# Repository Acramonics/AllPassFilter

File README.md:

All Pass Filter
===============

Circuit by Jake Rothman, Practical Electronics, June 2026

KiCad and PCB by Andrew Martin, acramonics, May 2026

Background
----------

This is a universal all-pass filter with 8 cascaded all-pass sections
allowing a frequency-dependent phase shift.

See the April, May and June 2026 issues of Practical Electronics for details.

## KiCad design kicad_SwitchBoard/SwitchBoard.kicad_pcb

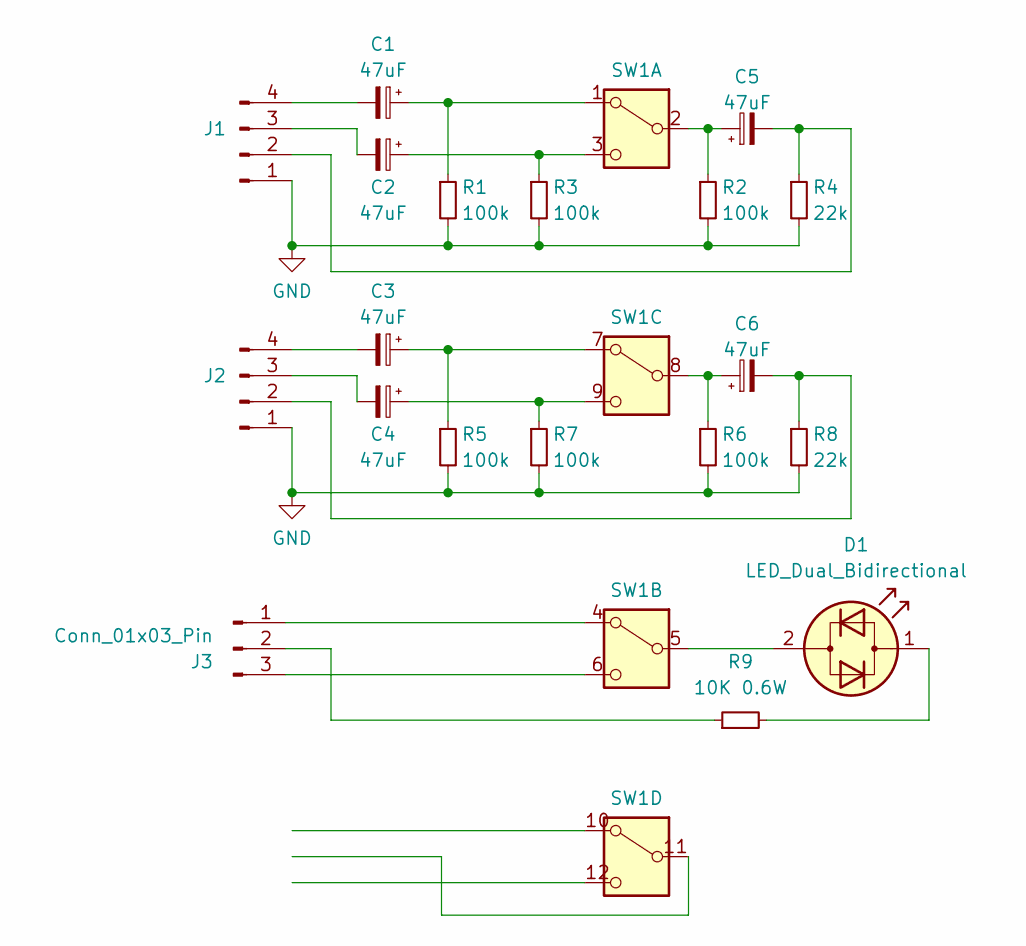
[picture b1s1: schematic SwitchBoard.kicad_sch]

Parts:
C1, C2, C3, C4, C5, C6: 47uF; CP_Radial_D5.0mm_P2.50mm
D1: LED_Dual_Bidirectional; LED_D5.0mm
J1, J2: Conn_01x04_Pin; Molex_KK-254_AE-6410-04A_1x04_P2.54mm_Vertical
J3: Conn_01x03_Pin; Molex_KK-254_AE-6410-03A_1x03_P2.54mm_Vertical
R1, R2, R3, R5, R6, R7: 100k; R_Axial_DIN0207_L6.3mm_D2.5mm_P10.16mm_Horizontal
R4, R8: 22k; R_Axial_DIN0207_L6.3mm_D2.5mm_P10.16mm_Horizontal
R9: 10K 0.6W; R_Axial_DIN0411_L9.9mm_D3.6mm_P12.70mm_Horizontal
SW1: SW_4PDT_x4; PushSwitch_4PDT_2x6Pin_P3.18x2.8

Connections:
GND: J1.1, J2.1, R1.2, R2.2, R3.2, R4.2, R5.2, R6.2, R7.2, R8.2
unnamed: D1.2 (AK), SW1.5 (B)
unnamed: D1.1 (KA), R9.2
unnamed: C5.2, J1.2, R4.1
unnamed: C2.2, J1.3
unnamed: C1.2, J1.4
unnamed: C6.2, J2.2, R8.1
unnamed: C4.2, J2.3
unnamed: C3.2, J2.4
unnamed: J3.1, SW1.4 (A)
unnamed: J3.2, R9.1
unnamed: J3.3, SW1.6 (C)
unnamed: C1.1, R1.1, SW1.1 (A)
unnamed: C5.1, R2.1, SW1.2 (B)
unnamed: C2.1, R3.1, SW1.3 (C)
unnamed: C3.1, R5.1, SW1.7 (A)
unnamed: C6.1, R6.1, SW1.8 (B)
unnamed: C4.1, R7.1, SW1.9 (C)

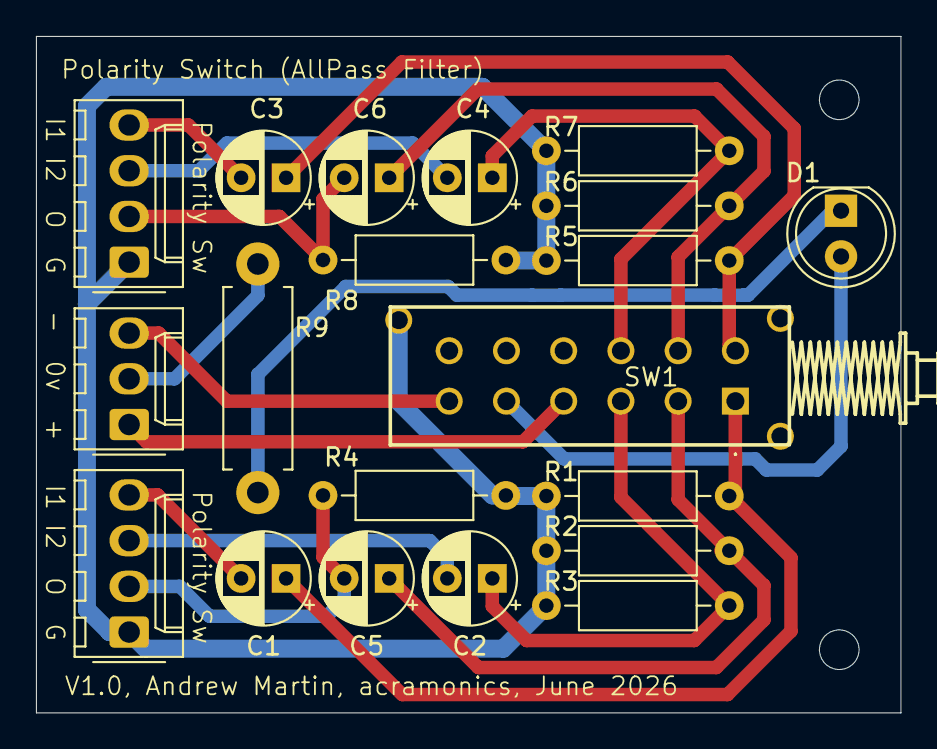
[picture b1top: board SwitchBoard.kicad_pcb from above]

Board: 2 copper layers, 48.0 x 37.6 mm, 20 parts (0 on the bottom side), 18 nets.

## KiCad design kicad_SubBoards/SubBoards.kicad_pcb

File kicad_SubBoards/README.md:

This uses the *SamacSys* footprint for the Alpha switch available via
the Mouser web site and directly from
[Component Search Engine](https://componentsearchengine.com/search?term=SR2612F-0112-21R0B-D8-N)

Using the Library
-----------------

First create a path name for the SamacSys Library:

1. In the main KiCad window, select `Preferences>Configure Paths`

2. Click the `+` sign and add a path called `KICAD_SAMACSYS_LIBS` and pointing to wherever the directory is containing the `SamacSys_Parts.lib` file.

3. Click OK

Next, configure the symbol library:

1. In the main KiCad window, select `Preferences>Manage Symbol Libraries`
2. Click the `+` sign and add a new library:

- `Nickname` = `SamacSys`
- `Library Path` = `${KICAD_SAMACSYS_LIBS}/SamacSys_Parts.kicad_sym`
- `Description` = `SamacSys Symbols`

and click `OK`.

Finally, configure the footprints library:

1. In the main KiCad window, select `Preferences>Manage Footprint Libraries`
2. Click the `+` sign and add a new library:

- `Nickname` = `SamacSys`
- `Library Path` = `${KICAD_SAMACSYS_LIBS}/SamacSys_Parts.pretty`
- `Description` = `SamacSys Footprints`

and click `OK`.

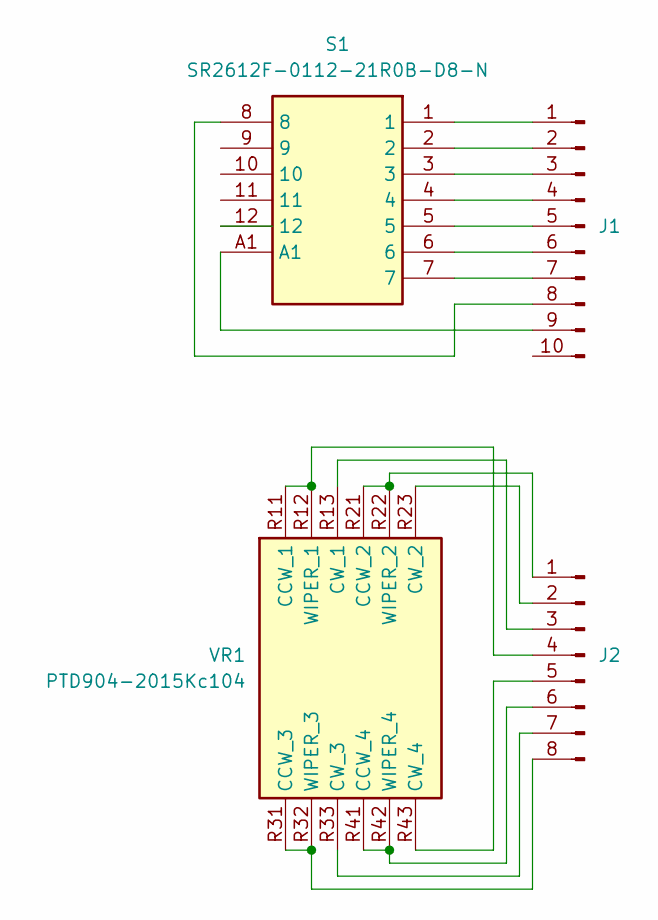
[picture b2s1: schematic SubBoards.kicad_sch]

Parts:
J1: Conn_01x10_Pin; Molex_KK-254_AE-6410-10A_1x10_P2.54mm_Vertical
J2: Conn_01x08_Pin; Molex_KK-254_AE-6410-08A_1x08_P2.54mm_Vertical
S1: SR2612F-0112-21R0B-D8-N; SR2612F011221R0BD8N; Mouser Part Number 105-SR2612F-12-21RN
VR1: PTD904-2015Kc104; PTD9042015Kc104; Manufacturer_Part_Number PTD904-2015Kc104; Mouser Part Number 652-PTD9042015KC104

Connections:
unnamed: J1.1, S1.1
unnamed: J1.2, S1.2
unnamed: J1.3, S1.3
unnamed: J1.4, S1.4
unnamed: J1.5, S1.5
unnamed: J1.6, S1.6
unnamed: J1.7, S1.7
unnamed: J1.8, S1.8
unnamed: J1.9, S1.A1
unnamed: J2.1, VR1.R21 (CCW_2), VR1.R22 (WIPER_2)
unnamed: J2.2, VR1.R23 (CW_2)
unnamed: J2.3, VR1.R13 (CW_1)
unnamed: J2.4, VR1.R11 (CCW_1), VR1.R12 (WIPER_1)
unnamed: J2.5, VR1.R43 (CW_4)
unnamed: J2.6, VR1.R41 (CCW_4), VR1.R42 (WIPER_4)
unnamed: J2.7, VR1.R33 (CW_3)
unnamed: J2.8, VR1.R31 (CCW_3), VR1.R32 (WIPER_3)

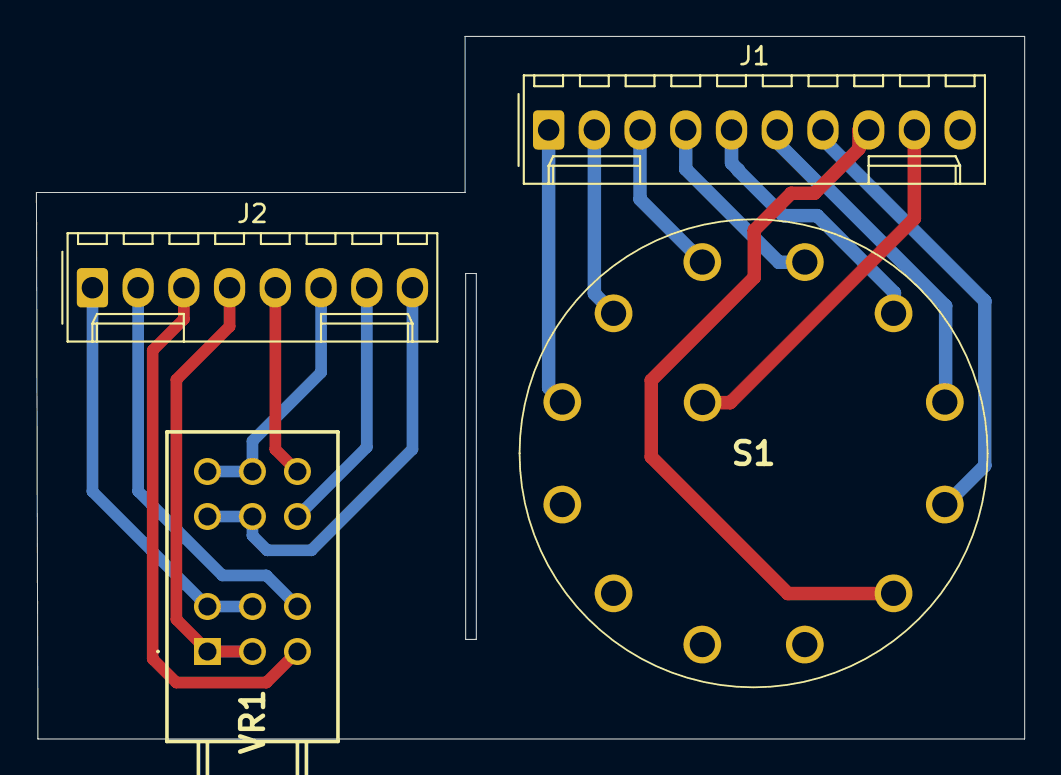
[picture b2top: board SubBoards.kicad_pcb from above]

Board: 2 copper layers, 54.9 x 39.0 mm, 4 parts (0 on the bottom side), 17 nets.

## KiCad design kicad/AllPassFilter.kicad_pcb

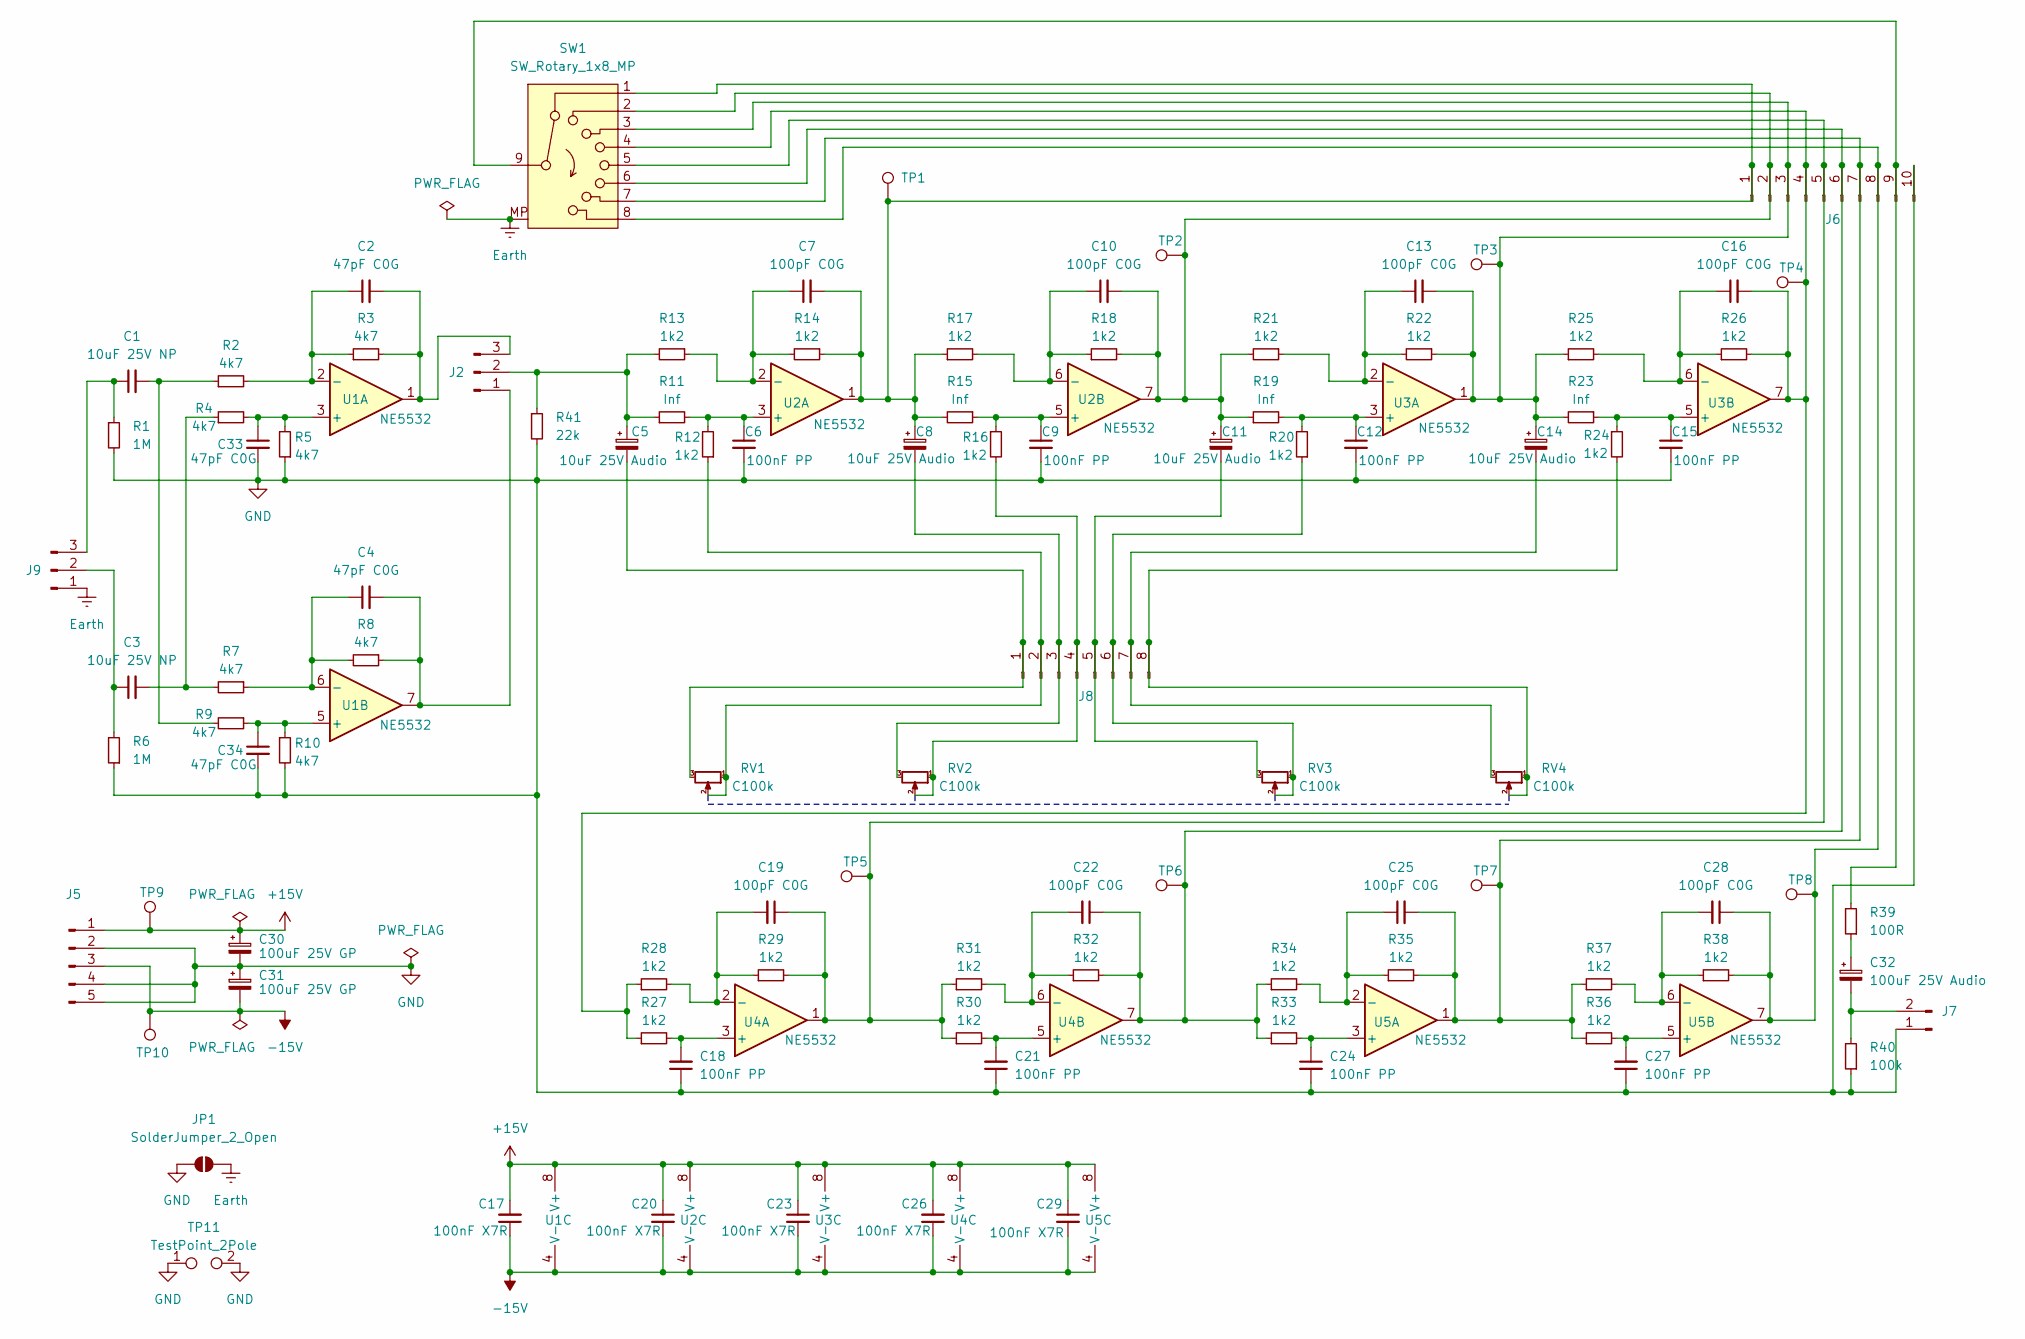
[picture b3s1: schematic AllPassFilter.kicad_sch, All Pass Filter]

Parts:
C1, C3: 10uF 25V NP; C_Radial_D4.0mm_H7.0mm_P1.50mm
C2, C4, C33, C34: 47pF C0G; C_Disc_D3.8mm_W2.6mm_P2.50mm
C5, C8, C11, C14: 10uF 25V Audio; CP_Radial_D4.0mm_P1.50mm
C6, C9, C12, C15, C18, C21, C24, C27: 100nF PP; C_Rect_L7.2mm_W5.5mm_P5.00mm_FKS2_FKP2_MKS2_MKP2
C7, C10, C13, C16, C19, C22, C25, C28: 100pF C0G; C_Disc_D5.1mm_W3.2mm_P5.00mm
C17, C20, C23, C26, C29: 100nF X7R; C_Rect_L7.2mm_W5.5mm_P5.00mm_FKS2_FKP2_MKS2_MKP2
C30, C31: 100uF 25V GP; CP_Radial_D6.3mm_P2.50mm
C32: 100uF 25V Audio; CP_Radial_D8.0mm_P3.50mm
J2, J9: Conn_01x03_Pin; Molex_KK-254_AE-6410-03A_1x03_P2.54mm_Vertical
J5: Conn_01x05_Pin; Molex_KK-254_AE-6410-05A_1x05_P2.54mm_Vertical
J6: Conn_01x10_Pin; Molex_KK-254_AE-6410-10A_1x10_P2.54mm_Vertical
J7: Conn_01x02_Pin; Molex_KK-254_AE-6410-02A_1x02_P2.54mm_Vertical
J8: Conn_01x08_Pin; Molex_KK-254_AE-6410-08A_1x08_P2.54mm_Vertical
JP1: SolderJumper_2_Open; SolderJumper-2_P1.3mm_Open_RoundedPad1.0x1.5mm
R1, R6: 1M; R_Axial_DIN0207_L6.3mm_D2.5mm_P10.16mm_Horizontal
R2, R3, R4, R5, R7, R8, R9, R10: 4k7; R_Axial_DIN0207_L6.3mm_D2.5mm_P10.16mm_Horizontal
R11, R15, R19, R23: Inf; R_Axial_DIN0207_L6.3mm_D2.5mm_P10.16mm_Horizontal
R12, R13, R14, R16, R17, R18, R20, R21, R22, R24, R25, R26, R27, R28, R29, R30, R31, R32, R33, R34, R35, R36, R37, R38: 1k2; R_Axial_DIN0207_L6.3mm_D2.5mm_P10.16mm_Horizontal
R39: 100R; R_Axial_DIN0207_L6.3mm_D2.5mm_P10.16mm_Horizontal
R40: 100k; R_Axial_DIN0207_L6.3mm_D2.5mm_P10.16mm_Horizontal
R41: 22k; R_Axial_DIN0207_L6.3mm_D2.5mm_P10.16mm_Horizontal
RV1, RV2, RV3, RV4: C100k
SW1: SW_Rotary_1x8_MP
TP1, TP2, TP3, TP4, TP5, TP6, TP7, TP8, TP9, TP10: TestPoint; TestPoint_THTPad_D1.5mm_Drill0.7mm
TP11: TestPoint_2Pole; TestPoint_Bridge_Pitch2.54mm_Drill0.7mm
U1, U2, U3, U4, U5: NE5532; DIP-8_W7.62mm

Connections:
+15V: C17.2, C20.1, C23.1, C26.2, C29.1, C30.1, J5.1, TP9.1, U1.8 (V+), U2.8 (V+), U3.8 (V+), U4.8 (V+), U5.8 (V+)
-15V: C17.1, C20.2, C23.2, C26.1, C29.2, C31.2, J5.3, TP10.1, U1.4 (V-), U2.4 (V-), U3.4 (V-), U4.4 (V-), U5.4 (V-)
Earth: J9.1, JP1.2 (B), SW1.MP
GND: C6.2, C9.2, C12.2, C15.2, C18.1, C21.1, C24.2, C27.1, C30.2, C31.1, C33.2, C34.2, J5.2, J5.4, J5.5, J6.10, J7.1, JP1.1 (A), R1.2, R5.1, R6.1, R10.2, R40.1, R41.2, TP11.1, TP11.2
unnamed: C1.2, R2.1, R9.2
unnamed: C3.2, R4.1, R7.2
unnamed: C32.1, R39.1
unnamed: C4.2, J2.1, R8.1, U1.7
unnamed: C5.1, J2.2, R11.1, R13.2, R41.1
unnamed: C2.2, J2.3, R3.2, U1.1
unnamed: C7.2, C8.1, J6.1, R14.1, R15.2, R17.1, SW1.1, TP1.1, U2.1
unnamed: C10.2, C11.1, J6.2, R18.2, R19.1, R21.2, SW1.2, TP2.1, U2.7
unnamed: C13.2, C14.1, J6.3, R22.1, R23.2, R25.1, SW1.3, TP3.1, U3.1
unnamed: C16.2, J6.4, R26.2, R27.1, R28.1, SW1.4, TP4.1, U3.7
unnamed: C19.1, J6.5, R29.2, R30.1, R31.1, SW1.5, TP5.1, U4.1
unnamed: C22.1, J6.6, R32.2, R33.1, R34.1, SW1.6, TP6.1, U4.7
unnamed: C25.2, J6.7, R35.2, R36.1, R37.1, SW1.7, TP7.1, U5.1
unnamed: C28.1, J6.8, R38.2, SW1.8, TP8.1, U5.7
unnamed: J6.9, R39.2, SW1.9
unnamed: C32.2, J7.2, R40.2
unnamed: C5.2, J8.1, RV1.3
unnamed: J8.2, R12.1, RV1.1, RV1.2
unnamed: C8.2, J8.3, RV2.3
unnamed: J8.4, R16.2, RV2.1, RV2.2
unnamed: C11.2, J8.5, RV3.3
unnamed: J8.6, R20.1, RV3.1, RV3.2
unnamed: C14.2, J8.7, RV4.3
unnamed: J8.8, R24.2, RV4.1, RV4.2
unnamed: C3.1, J9.2, R6.2
unnamed: C1.1, J9.3, R1.1
unnamed: C33.1, R4.2, R5.2, U1.3 (+)
unnamed: C2.1, R2.2, R3.1, U1.2 (-)
unnamed: C34.1, R9.1, R10.1, U1.5 (+)
unnamed: C4.1, R7.1, R8.2, U1.6 (-)
unnamed: C6.1, R11.2, R12.2, U2.3 (+)
unnamed: C7.1, R13.1, R14.2, U2.2 (-)
unnamed: C9.1, R15.1, R16.1, U2.5 (+)
unnamed: C10.1, R17.2, R18.1, U2.6 (-)
unnamed: C12.1, R19.2, R20.2, U3.3 (+)
unnamed: C13.1, R21.1, R22.2, U3.2 (-)
unnamed: C15.1, R23.1, R24.1, U3.5 (+)
unnamed: C16.1, R25.2, R26.1, U3.6 (-)
unnamed: C18.2, R27.2, U4.3 (+)
unnamed: C19.2, R28.2, R29.1, U4.2 (-)
unnamed: C21.2, R30.2, U4.5 (+)
unnamed: C22.2, R31.2, R32.1, U4.6 (-)
unnamed: C24.1, R33.2, U5.3 (+)
unnamed: C25.1, R34.2, R35.1, U5.2 (-)
unnamed: C27.2, R36.2, U5.5 (+)
unnamed: C28.2, R37.2, R38.1, U5.6 (-)

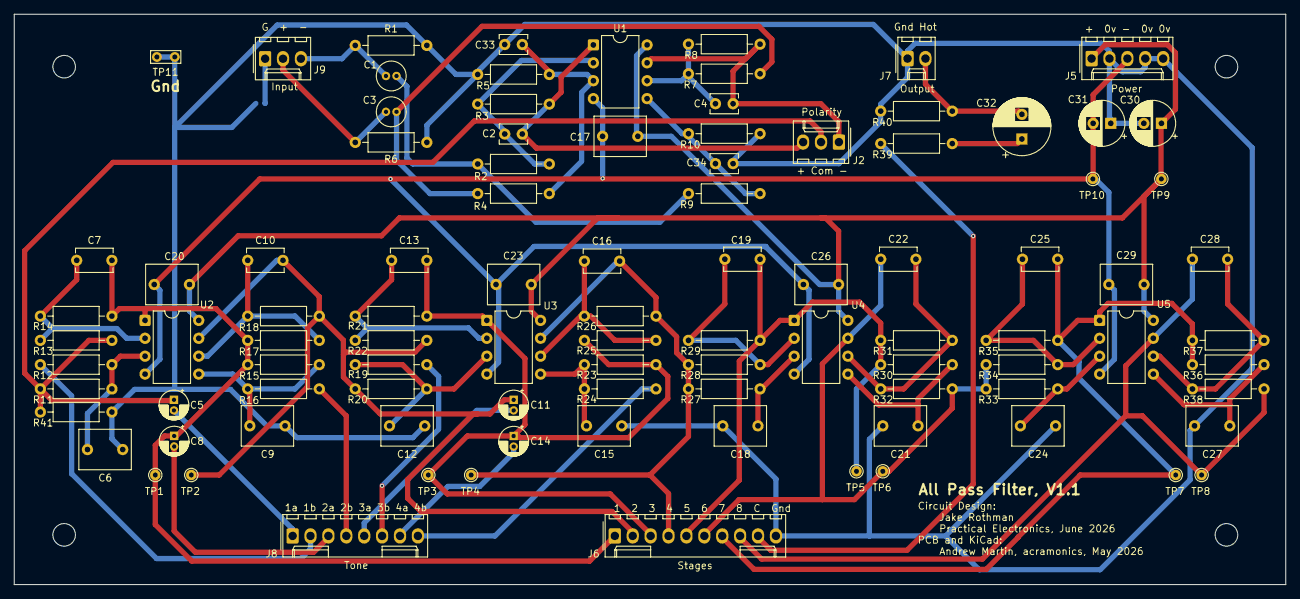
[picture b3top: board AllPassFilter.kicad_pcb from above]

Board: 2 copper layers, 180.4 x 80.9 mm, 98 parts (1 on the bottom side), 50 nets.

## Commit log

2026-05-20 Complete version
2026-05-20 Added readme
2026-05-20 Added start of SubBoards
2026-05-26 Completed subboards
2026-05-26 Updated BOM
2026-06-07 Added polarity switch board
2026-06-13 Update for new switch
2026-06-14 Completed V1.0
2026-06-29 Added schematic PDF
